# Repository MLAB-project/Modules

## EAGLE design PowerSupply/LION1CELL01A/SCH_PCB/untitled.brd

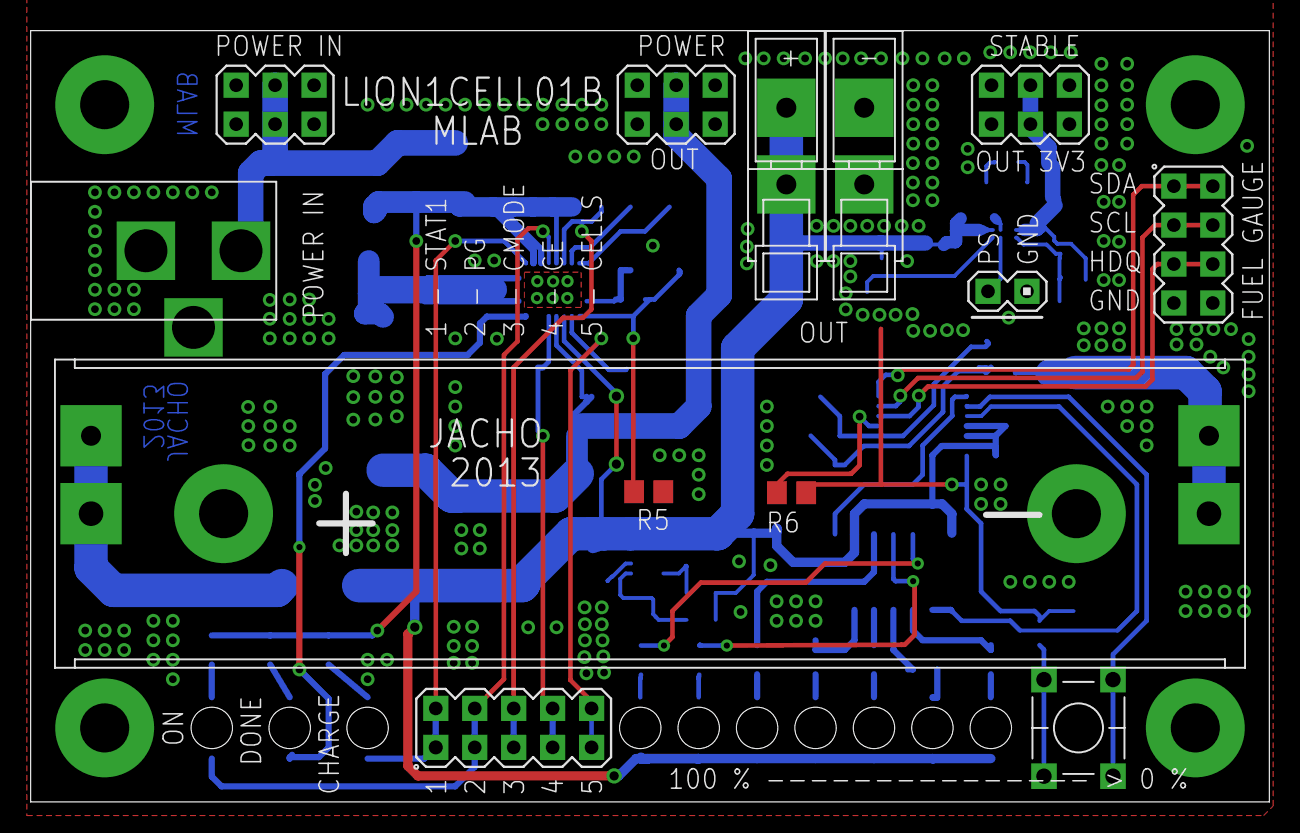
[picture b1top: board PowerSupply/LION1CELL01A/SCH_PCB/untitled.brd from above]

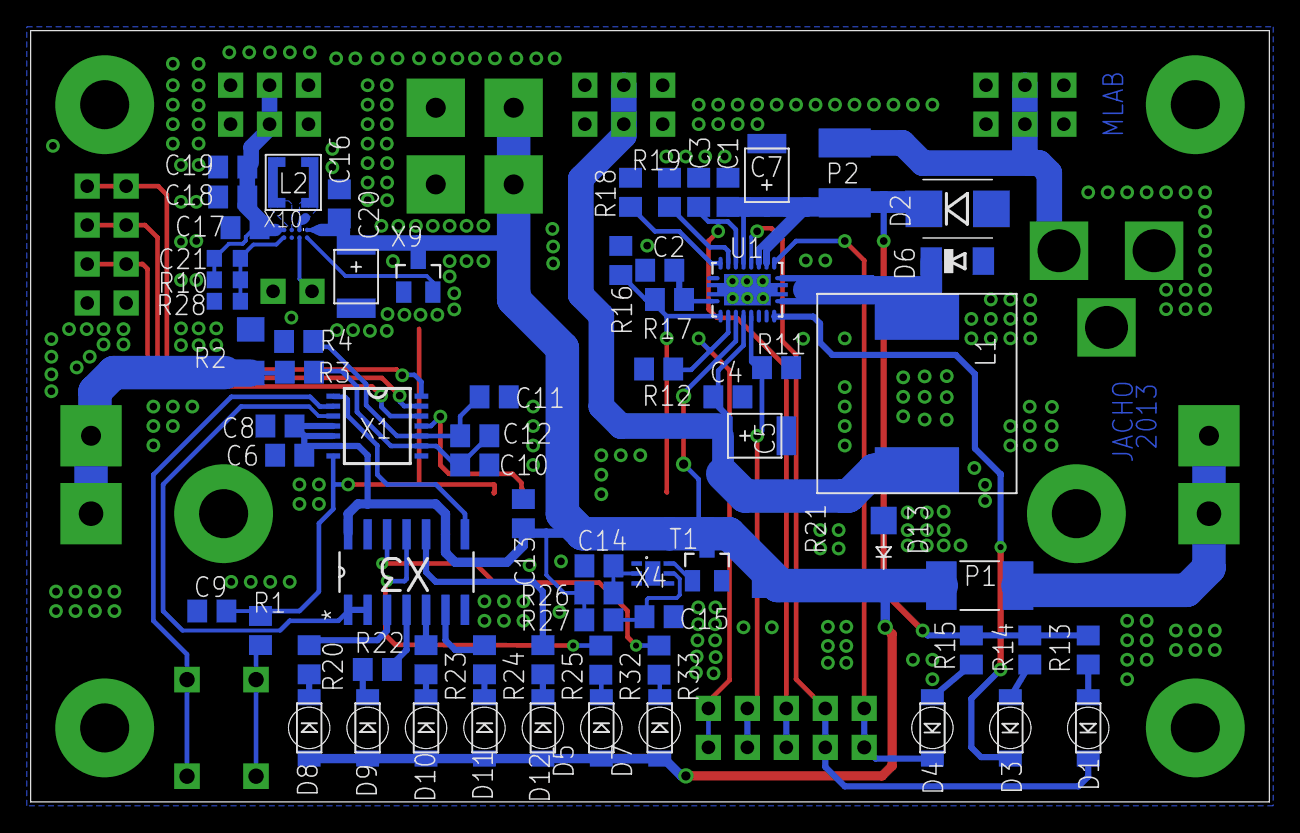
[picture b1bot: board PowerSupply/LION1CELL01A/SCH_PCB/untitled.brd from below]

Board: 2 copper layers, 80.8 x 50.3 mm, 87 parts (70 on the bottom side), 55 nets.

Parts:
C1, C2, C3, C4, C6, C8, C10, C11, C12, C13, C14, C15: 100nF; C0805
C5, C7: 10uF; B
C9: 1u; C0805
C16: 10uF; C0805
C17, C18, C19: 10u; C0805
C20: 47uF; B
C21: 10p; 0603
D1, D3, D4, D5, D7, D8, D9, D10, D11, D12: 1206_2
D2: M4; SMB
D6: ZSMD-5V6; MINIMELF
D13: SMA
L1: DE1205-10
L2: LPS3015-152MLC; LPS3015
P1: BSMD; 2410
P2: 1812
R1: 1K; 0805
R2: 0,01 75ppm; 1206
R3, R4: 100R; 0805
R5, R6: NCP21XV103J03RA; 0805
R10: 287k; 0603
R11, R12: 10k; 0805
R13, R14, R15, R20, R22, R23, R24, R25, R32, R33: 270R; 0805
R16: 442k; 0805
R17: 9k31; 0805
R18, R19, R26, R27: 7k5; 0805
R21: 0R1; R2512
R28: 51k1; 0603
SV1, SV2, SV5: MA03-2
SV3: MA04-2
SV4: MA05-2
SV6: MA02-1
SV7, SV8: WAGO256
SW1: TACT-64K
T1: IRLML6244; SOT23
U1: BQ24103; RHL_R-VQFN-N20
U$2: LION1
X1: BQ34Z100PW; TSSOP14
X2: DC2.1MM
X3: SN74HC164D; SOIC127P600X175-14N
X4: SON_N6
X5, X6, X7, X8: SROUB3M
X9: SOT23
X10: DSBGA8

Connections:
+BAT: C6.1, C8.1, C13.2, C16.2, C20.+, D5.A, D7.A, D8.A, D9.A, D10.A, D11.A, D12.A, D13.K, P1.2, R21.2, R26.2, R27.2, SV7.1, SV7.A1, T1.3, U1.14, X1.4, X1.5, X1.6, X3.9, X3.14, X9.3, X10.A1
+BAT2: C4.1, C5.+, L1.P$2, R21.1, SV2.3, SV2.4, U1.15
EN: X9.2, X10.A2
GND: C1.2, C2.2, C3.2, C4.2, C5.-, C6.2, C7.-, C8.2, C9.2, C10.2, C11.2, C13.1, C14.2, C15.2, C16.1, C17.1, C18.1, C19.1, C20.-, D2.A, D6.A, D13.A, R2.1, R4.1, R5.1, R11.1, R12.1, R16.1, R18.1, R19.1, R28.1, SV1.1, SV1.2, SV1.5, SV1.6, SV2.1, SV2.2, SV2.5, SV2.6, SV3.7, SV3.8, SV5.1, SV5.2, SV5.5, SV5.6, SV6.2, SV8.1, SV8.A1, T1.2, U1.10, U1.17, U1.18, X1.8, X2.GND, X3.7, X4.3, X4.4, X4.7, X9.1, X10.C2
unnamed: C1.1, C7.+, D2.K, P2.2, R13.2, R14.2, R15.2, U1.3, U1.4, U1.6
unnamed: P1.1, U$2.+, U$2.+1
unnamed: D6.C, L1.P$1, U1.1, U1.20
unnamed: D4.K, SV4.1, SV4.2, U1.2
unnamed: D3.K, U1.19
unnamed: D1.K, SV4.3, SV4.4, U1.5
unnamed: D1.A, R13.1
unnamed: D3.A, R14.1
unnamed: D4.A, R15.1
unnamed: R12.2, SV4.9, SV4.10, U1.13
unnamed: R11.2, SV4.7, SV4.8, U1.16
unnamed: C2.1, R17.2, U1.11
unnamed: R18.2, U1.9
unnamed: C3.1, SV4.5, SV4.6, U1.7
unnamed: R19.2, U1.8
unnamed: SV3.3, SV3.4, X1.13
unnamed: SW1.P$3, SW1.P$4, X1.2
unnamed: R5.2, R16.2, R17.1, U1.12
unnamed: L2.1-1, L2.1-2, L2.1-3, X10.B1
unnamed: R1.1, SW1.P$1, SW1.P$2
unnamed: SV6.1, X10.B2
unnamed: R6.2, X1.11
unnamed: C10.1, C12.2, R3.2, X1.9
unnamed: SV3.5, SV3.6, X1.12
unnamed: SV3.1, SV3.2, X1.14
unnamed: L2.2-1, L2.2-2, L2.2-3, X10.C1
unnamed: C11.1, C12.1, R4.2, X1.10
unnamed: C17.2, C18.2, C19.2, C21.2, R10.2, SV5.3, SV5.4, X10.D1
unnamed: C21.1, R10.1, R28.2, X10.D2
unnamed: R20.1, X3.3
unnamed: D8.K, R20.2
unnamed: R22.1, X3.4
unnamed: R23.1, X3.5
unnamed: R24.1, X3.6
unnamed: R25.1, X3.10
unnamed: D9.K, R22.2
unnamed: D11.K, R24.2
unnamed: D12.K, R25.2
unnamed: D10.K, R23.2
unnamed: C14.1, R26.1, X4.2
unnamed: C15.1, R27.1, X4.5
unnamed: T1.1, X4.6
unnamed: R32.1, X3.11
unnamed: R33.1, X3.12
unnamed: D5.K, R32.2
unnamed: D7.K, R33.2
unnamed: P2.1, SV1.3, SV1.4, X2.+
P1: X1.3, X3.1, X3.2
P2: X1.1, X3.8
R2: R2.2, R3.1, U$2.-, U$2.-1
REG25: C9.1, R1.2, R6.1, X1.7

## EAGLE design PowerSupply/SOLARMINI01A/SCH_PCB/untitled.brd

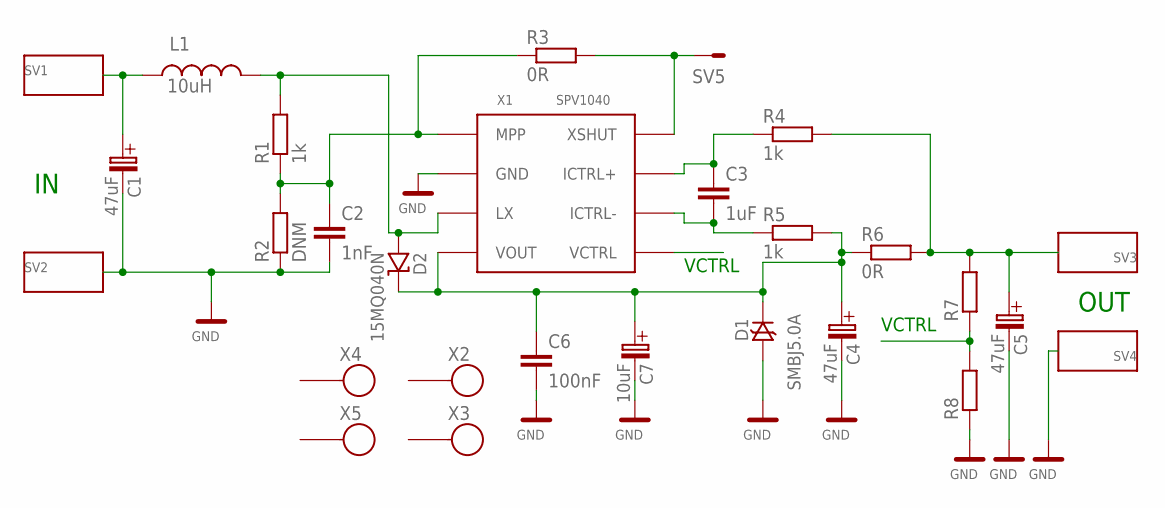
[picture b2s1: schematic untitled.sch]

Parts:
C1, C4, C5: 47uF; C
C2: 1nF; C0805
C3: 1uF; C0805
C6: 100nF; C0805
C7: 10uF; B
D1: SMBJ5.0A; SMB
D2: 15MQ040N; SMA
L1: 10uH; DE1205-10
R1, R4, R5: 1k; 0805
R2: DNM; 0805
R3, R6: 0R; 1206
R7, R8: R0805; 0805
SV1, SV2, SV3, SV4: WAGO256
SV5: MA01-1
X1: SPV1040; TSSOP8
X2, X3, X4, X5: SROUB3M

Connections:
GND: C1.- (C_EL-), C2.2, C4.- (C_EL-), C5.- (C_EL-), C6.2, C7.- (C_EL-), D1.A, R2.1, R8.1, SV2.1, SV2.A1, SV4.1, SV4.A1, X1.2 (GND)
unnamed: C1.+ (C_EL+), L1.P$1 (1), SV1.1, SV1.A1
unnamed: R3.2, SV5.1, X1.8 (XSHUT)
unnamed: C2.1, R1.1, R2.2, R3.1, X1.1 (MPP)
unnamed: C3.1, R4.1, X1.7 (ICTRL+)
unnamed: C4.+ (C_EL+), C6.1, C7.+ (C_EL+), D1.K, D2.K, R5.2, R6.1, X1.4 (VOUT)
unnamed: D2.A, L1.P$2 (2), R1.2, X1.3 (LX)
unnamed: C5.+ (C_EL+), R4.2, R6.2, R7.2, SV3.1, SV3.A1
unnamed: C3.2, R5.1, X1.6 (ICTRL-)
VCTRL: R7.1, R8.2, X1.5 (VCTRL)

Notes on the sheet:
VCTRL
OUT

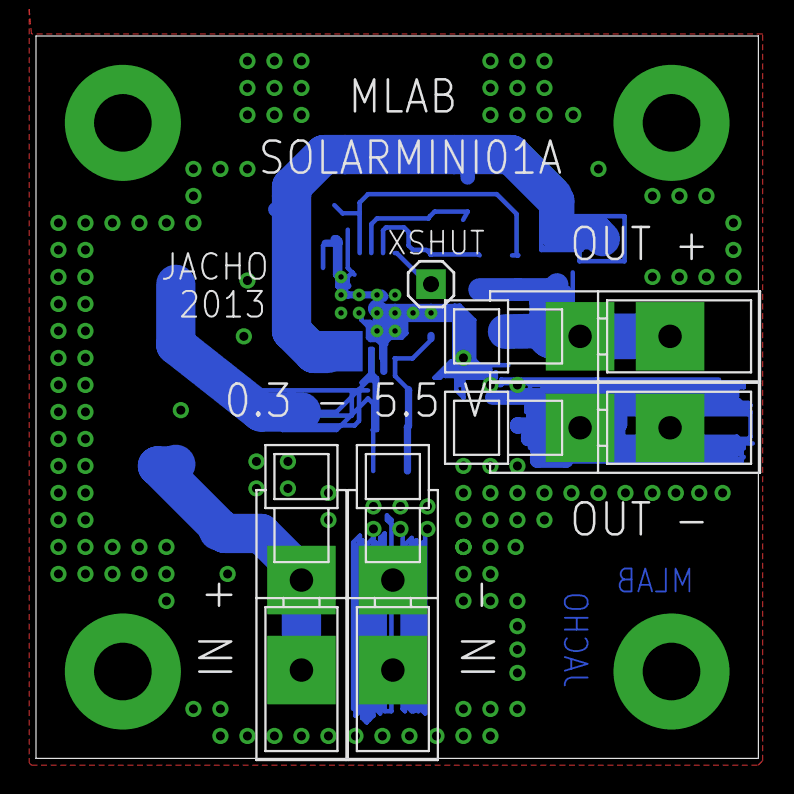
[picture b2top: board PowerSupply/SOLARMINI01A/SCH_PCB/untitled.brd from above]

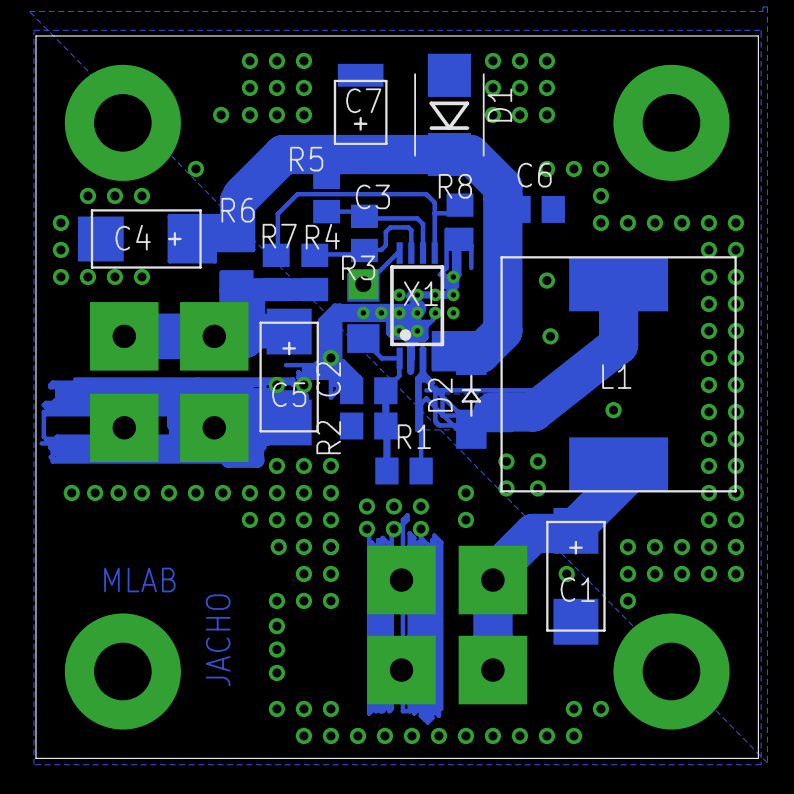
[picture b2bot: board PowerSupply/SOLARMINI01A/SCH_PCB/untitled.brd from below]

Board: 2 copper layers, 40.1 x 40.1 mm, 28 parts (19 on the bottom side), 10 nets.

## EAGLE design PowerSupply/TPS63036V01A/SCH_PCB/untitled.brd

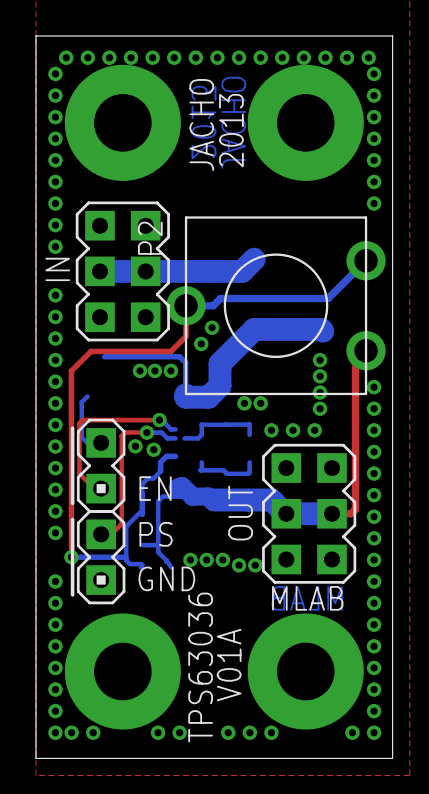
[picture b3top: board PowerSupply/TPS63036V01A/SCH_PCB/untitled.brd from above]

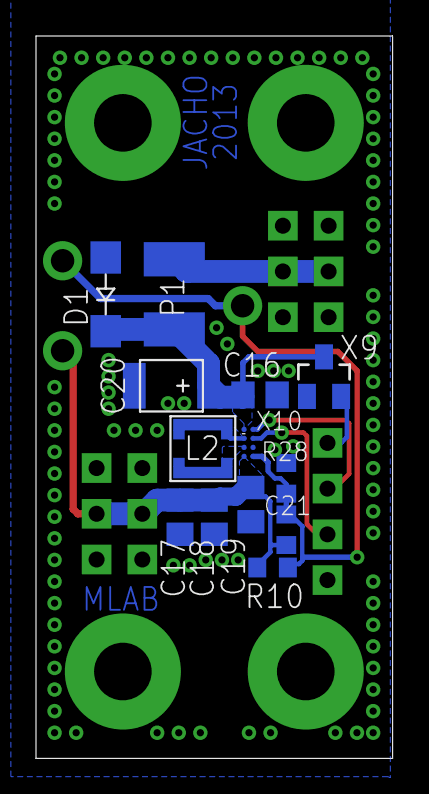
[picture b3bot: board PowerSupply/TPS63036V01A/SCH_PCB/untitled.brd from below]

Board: 2 copper layers, 19.8 x 40.1 mm, 22 parts (13 on the bottom side), 10 nets.

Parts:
C16: 10uF; C0805
C17, C18, C19: 10u; C0805
C20: 47uF; B
C21: 10p; 0603
D1: SMA
L2: LPS3015-152MLC; LPS3015
P1: 1812
P2: TRIM_CA9MTV10
R10: 287k; 0603
R28: 51k1; 0603
SV1, SV6: MA02-1
SV3, SV5: MA03-2
X1, X2, X3, X4: SROUB3M
X9: SOT23
X10: DSBGA8

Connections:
+BAT2: C16.2, C20.+, D1.K, P1.2, X9.3, X10.A1
GND: C16.1, C17.1, C18.1, C19.1, C20.-, D1.A, R28.1, SV3.1, SV3.2, SV3.5, SV3.6, SV5.1, SV5.2, SV5.5, SV5.6, SV6.2, X1.P$1, X2.P$1, X3.P$1, X4.P$1, X9.1, X10.C2
unnamed: SV1.1, X9.2
unnamed: SV1.2, X10.A2
unnamed: P1.1, SV3.3, SV3.4
unnamed: L2.1-1, L2.1-2, L2.1-3, X10.B1
unnamed: SV6.1, X10.B2
unnamed: L2.2-1, L2.2-2, L2.2-3, X10.C1
unnamed: C17.2, C18.2, C19.2, C21.2, P2.1, R10.2, SV5.3, SV5.4, X10.D1
unnamed: C21.1, P2.2, P2.3, R10.1, R28.2, X10.D2

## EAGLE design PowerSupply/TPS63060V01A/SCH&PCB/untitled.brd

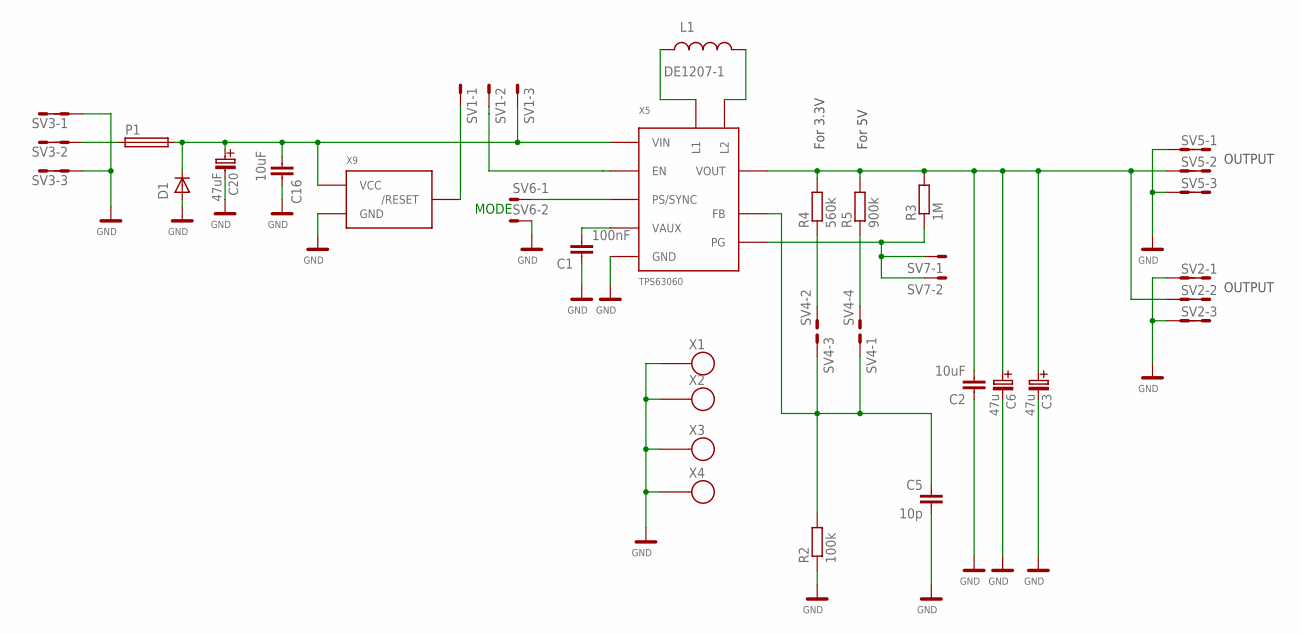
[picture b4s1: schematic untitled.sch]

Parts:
C1: 100nF; C0805
C2, C16: 10uF; C0805
C3, C6: 47u; C
C5: 10p; C0805
C20: 47uF; C
D1: D-OB.SMA; SMA
L1: DE1207-1; DE1205-10
P1: POJISTKA_1812; 1812
R2: 100k; 0805
R3: 1M; 0805
R4: 560k; 0805
R5: 900k; 0805
SV1: MA03-1
SV2, SV3, SV5: MA03-2
SV4: MA02-3; MA02-2
SV6, SV7: MA02-1
X1, X2, X3, X4: SROUB3M
X5: TPS63060; SON10
X9: APX809-26SA; SOT23

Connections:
+BAT2: C16.2, C20.+ (C_EL+), D1.K (C), P1.2, SV1.3, X5.2 (VIN), X9.3 (VCC)
GND: C1.1, C2.1, C3.- (C_EL-), C5.2, C6.- (C_EL-), C16.1, C20.- (C_EL-), D1.A, R2.1, SV2.1, SV2.2, SV2.5, SV2.6, SV3.1, SV3.2, SV3.5, SV3.6, SV5.1, SV5.2, SV5.5, SV5.6, SV6.2, X1.P$1, X2.P$1, X3.P$1, X4.P$1, X5.7 (GND), X5.11 (GND), X5.12 (GND), X5.13 (GND), X5.14 (GND), X5.15 (GND), X5.16 (GND), X5.17 (GND), X5.18 (GND), X5.19 (GND), X5.P$1 (GND), X5.P$2 (GND), X5.P$3 (GND), X5.P$4 (GND), X5.P$5 (GND), X9.1 (GND)
unnamed: SV1.1, X9.2 (/RESET)
unnamed: SV1.2, X5.3 (EN)
unnamed: P1.1, SV3.3, SV3.4
unnamed: C5.1, R2.2, SV4.1, SV4.3, X5.8 (FB)
unnamed: R3.1, SV7.1, SV7.2, X5.5 (PG)
unnamed: R4.1, SV4.2
unnamed: C2.2, C3.+ (C_EL+), C6.+ (C_EL+), R3.2, R4.2, R5.2, SV2.3, SV2.4, SV5.3, SV5.4, X5.9 (VOUT)
unnamed: R5.1, SV4.4
unnamed: SV6.1, X5.4 (PS/SYNC)
unnamed: C1.2, X5.6 (VAUX)
unnamed: L1.P$1 (1), X5.1 (L1)
unnamed: L1.P$2 (2), X5.10 (L2)

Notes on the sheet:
OUTPUT
MODE
For 5V
For 3.3V

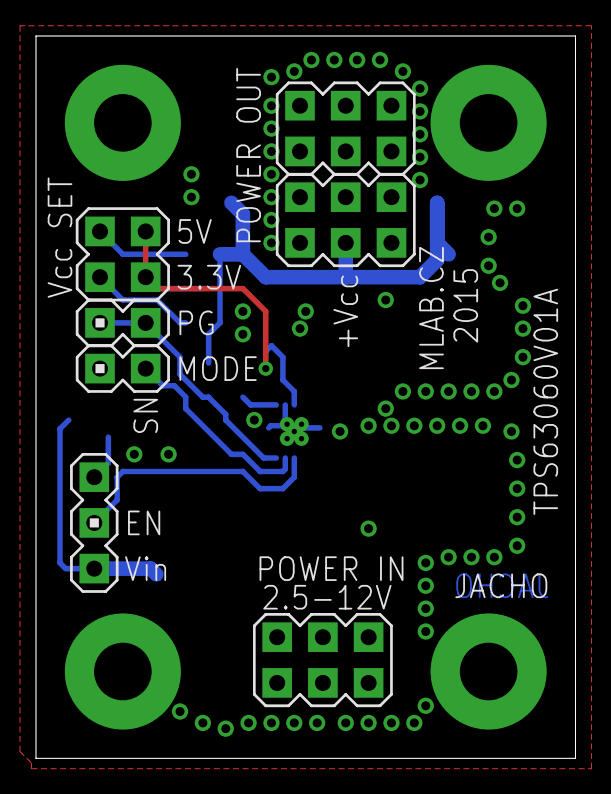
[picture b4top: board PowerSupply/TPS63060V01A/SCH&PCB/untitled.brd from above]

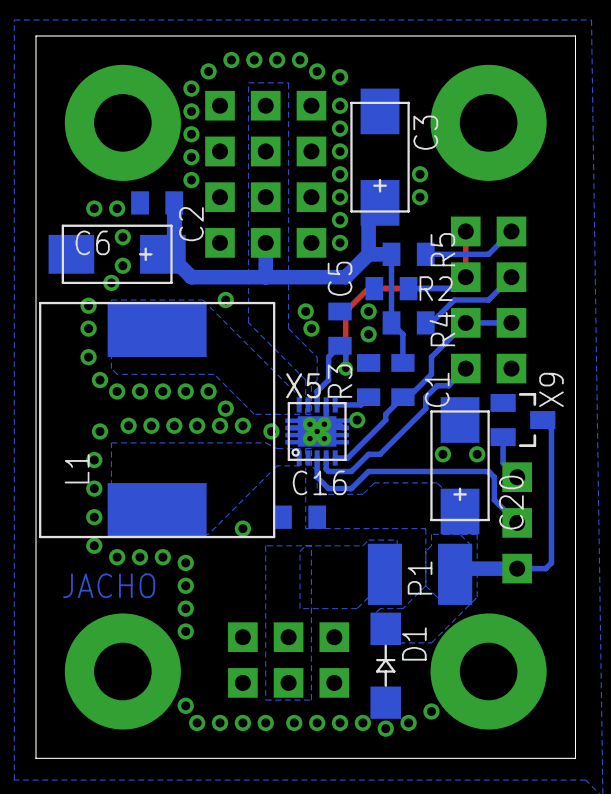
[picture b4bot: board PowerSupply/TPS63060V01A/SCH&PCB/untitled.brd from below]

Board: 2 copper layers, 30.0 x 40.1 mm, 27 parts (16 on the bottom side), 14 nets.

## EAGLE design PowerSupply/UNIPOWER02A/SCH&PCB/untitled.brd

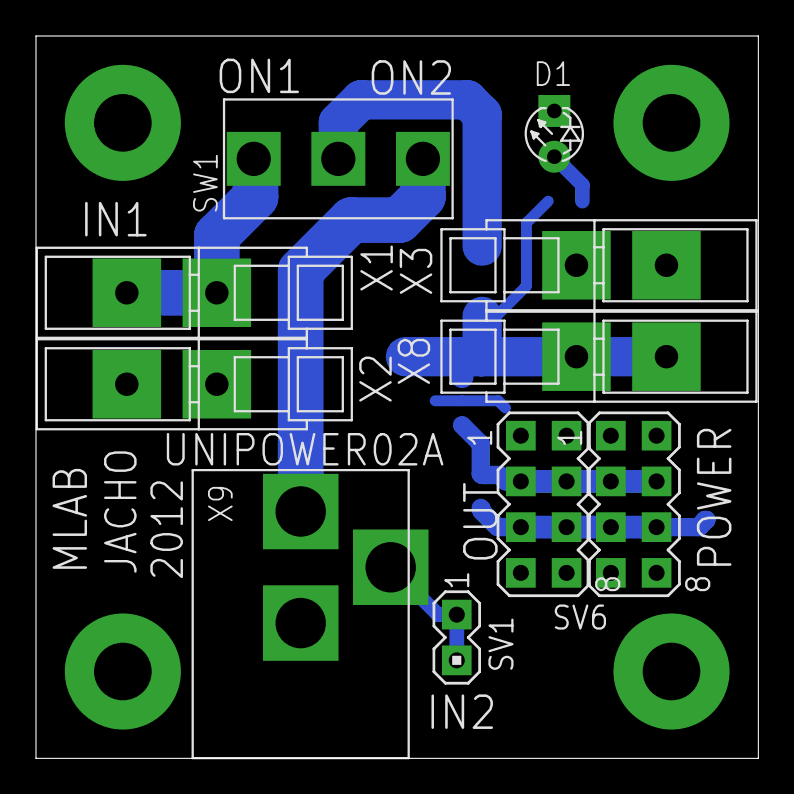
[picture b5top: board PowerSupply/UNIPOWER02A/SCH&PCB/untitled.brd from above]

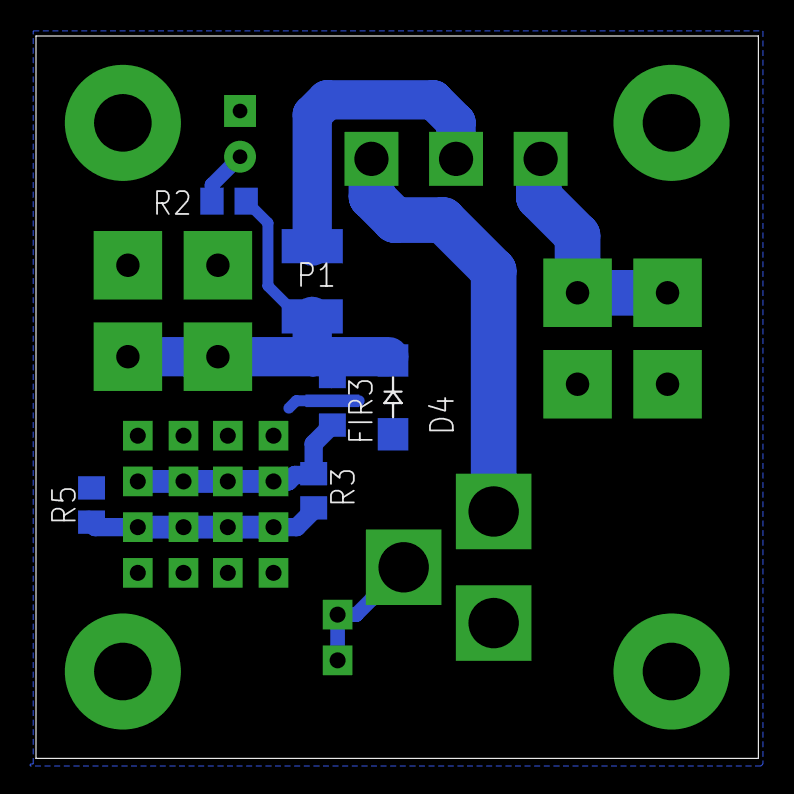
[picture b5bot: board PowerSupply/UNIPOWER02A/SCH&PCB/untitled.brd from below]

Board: 2 copper layers, 40.1 x 40.1 mm, 20 parts (6 on the bottom side), 9 nets.

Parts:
D1: D_LED_3
D4: M4; SMA
FIR3: F0805
P1: 1812
R2: R0805
R3: 0R pro 12V; R0805
R5: 0R pro 5V; R0805
SV1: MA02-1
SV5: JUMP2*4; MA04-2
SV6: JUMP2X4; MA04-2
SW1: PREPINAC-POSUVNÝ
X1, X2, X3, X8: WAGO256
X4, X5, X6, X7: M3; SROUB3M
X9: DC 2.1MM; KONEKTOR_DC_2.1MM

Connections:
+12V: SW1.1, X9.+
GND12: D1.K, D4.A, FIR3.2, R5.2, SV5.1, SV5.2, SV5.7, SV5.8, SV6.1, SV6.2, SV6.7, SV6.8, X2.1, X2.A1, X3.1, X3.A1, X9.GND1
unnamed: SW1.3, X1.1, X1.A1
unnamed: D1.A, R2.1
unnamed: R3.1, R5.1, SV5.5, SV5.6, SV6.5, SV6.6
unnamed: SV1.1, SV1.2, X9.GND
unnamed: FIR3.3, R3.2, SV5.3, SV5.4, SV6.3, SV6.4
unnamed: P1.1, SW1.2
unnamed: D4.K, FIR3.1, P1.2, R2.2, X8.1, X8.A1

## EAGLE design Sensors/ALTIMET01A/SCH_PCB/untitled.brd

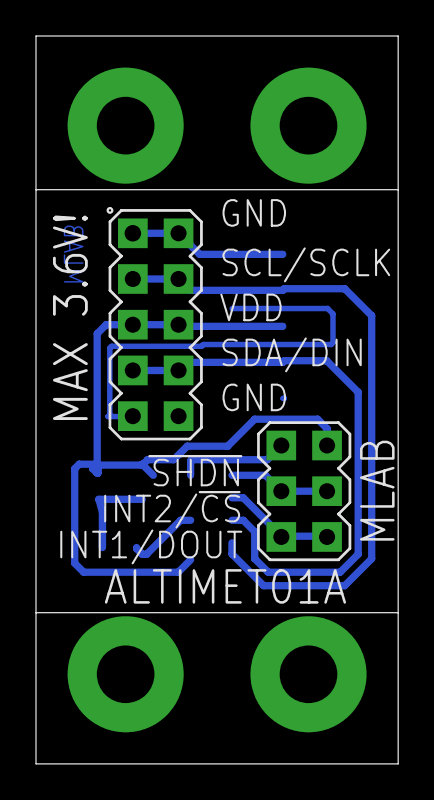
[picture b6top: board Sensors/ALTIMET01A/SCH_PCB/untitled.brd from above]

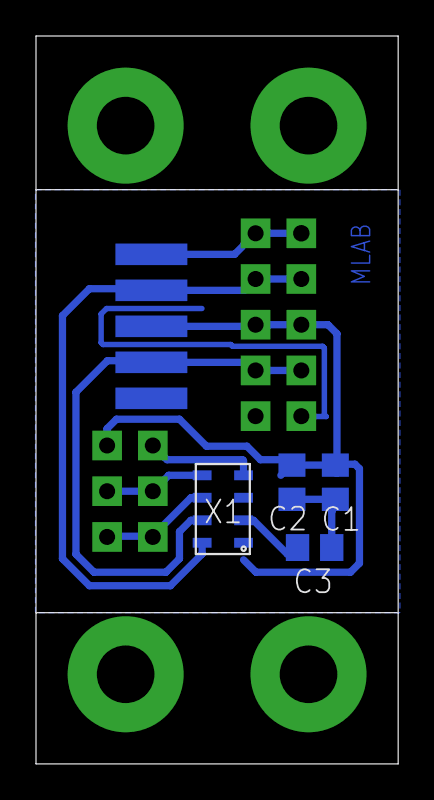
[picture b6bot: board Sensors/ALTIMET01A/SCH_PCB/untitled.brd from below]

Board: 2 copper layers, 20.1 x 40.4 mm, 11 parts (5 on the bottom side), 8 nets.

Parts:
C1, C3: 100nF; C0805
C2: 10uF; C0805
SV1: MA05-2
SV3: SMD_MA05-1
SW1: MA03-2
X1: MPL3115A2; LGA
X2, X3, X4, X5: SROUB3M

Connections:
GND: C1.2, C2.2, C3.2, SV1.1, SV1.2, SV1.9, SV1.10, SV3.1, SV3.5, X1.GND
INT1: SW1.1, SW1.2, X1.INT1
INT2: SW1.3, SW1.4, X1.INT2
unnamed: SW1.6, X1.VDDIO
unnamed: C3.1, X1.CAP
SCL: SV1.3, SV1.4, SV3.4, X1.SCL
SDA: SV1.7, SV1.8, SV3.2, X1.SDA
VCC: C1.1, C2.1, SV1.5, SV1.6, SV3.3, SW1.5, X1.VDD

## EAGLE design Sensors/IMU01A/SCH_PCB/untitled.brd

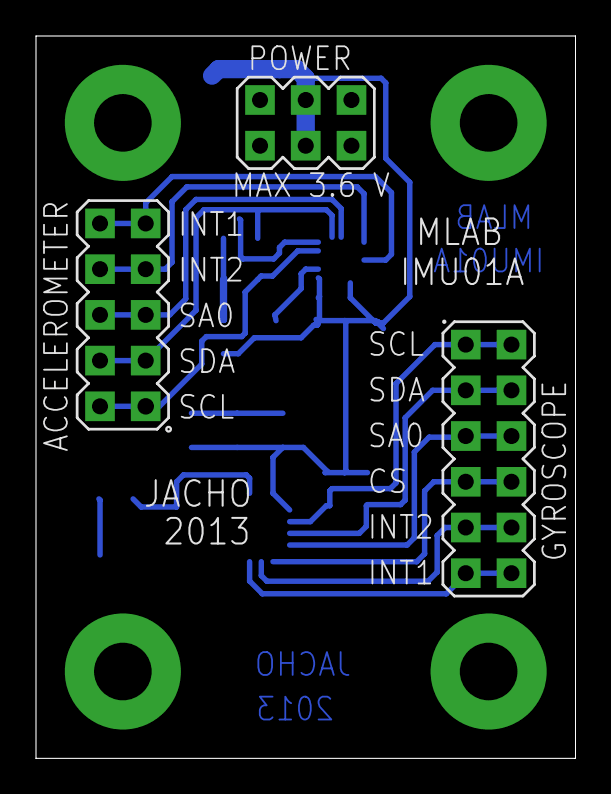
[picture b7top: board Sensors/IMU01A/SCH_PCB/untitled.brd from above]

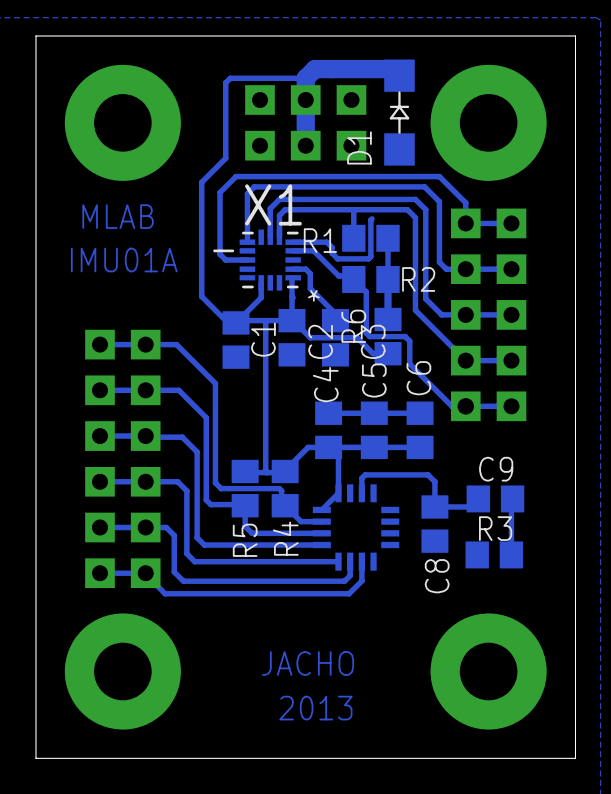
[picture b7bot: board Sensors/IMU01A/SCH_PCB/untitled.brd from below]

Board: 2 copper layers, 30.0 x 40.1 mm, 24 parts (17 on the bottom side), 17 nets.

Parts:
C1, C5, C6: 4u7; C0805
C2, C3, C4: 100n; C0805
C8: 10nF; C0805
C9: 470nF; C0805
D1: SMA
R1, R2: 4k7; R0805
R3, R4, R5: 10k; R0805
R6: 0R; R0805
SV1: MA03-2
SV2: MA06-2
SV3: MA05-2
X1: MMA8451Q; QFN50P300X300X100-16N
X2: A3G4250D; LGA16
X3, X4, X5, X6: SROUB3M

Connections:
+VCC: C1.1, C2.1, C4.1, C5.1, C6.1, D1.K, R4.1, R5.1, R6.1, SV1.3, SV1.4, X1.1, X1.14, X2.1, X2.16
GND: C1.2, C2.2, C3.2, C4.2, C5.2, C6.2, C8.2, D1.A, R3.1, SV1.1, SV1.2, SV1.5, SV1.6, X1.3, X1.5, X1.8, X1.10, X1.12, X1.13, X1.15, X1.16, X2.8, X2.9, X2.10, X2.11, X2.12, X2.13, X2.15
unnamed: R1.2, SV3.3, SV3.4, X1.6
unnamed: R2.2, SV3.1, SV3.2, X1.4
unnamed: SV3.5, SV3.6, X1.7
unnamed: C8.1, C9.1, X2.14
unnamed: C3.1, X1.2
unnamed: SV2.5, SV2.6, X2.4
unnamed: R1.1, R2.1, R6.2
unnamed: SV2.7, SV2.8, X2.5
unnamed: SV2.11, SV2.12, X2.7
unnamed: SV2.9, SV2.10, X2.6
unnamed: SV3.9, SV3.10, X1.11
unnamed: SV3.7, SV3.8, X1.9
unnamed: R4.2, SV2.1, SV2.2, X2.2
unnamed: C9.2, R3.2
unnamed: R5.2, SV2.3, SV2.4, X2.3

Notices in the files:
parts and their libraries:
PaJa_22: Copyright (C) PaJa 2001-2010
